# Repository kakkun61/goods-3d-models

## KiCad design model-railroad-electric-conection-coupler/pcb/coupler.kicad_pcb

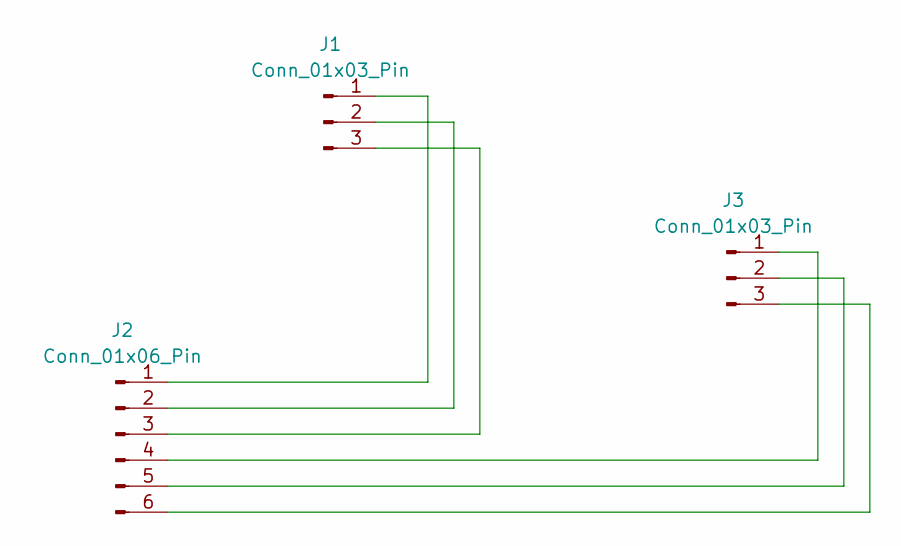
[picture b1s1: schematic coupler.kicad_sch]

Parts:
J1, J3: Conn_01x03_Pin; Pin_Side
J2: Conn_01x06_Pin; Molex_PicoBlade_53048-0610_1x06_P1.25mm_Horizontal

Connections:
unnamed: J1.1, J2.1
unnamed: J1.2, J2.2
unnamed: J1.3, J2.3
unnamed: J2.4, J3.1
unnamed: J2.5, J3.2
unnamed: J2.6, J3.3

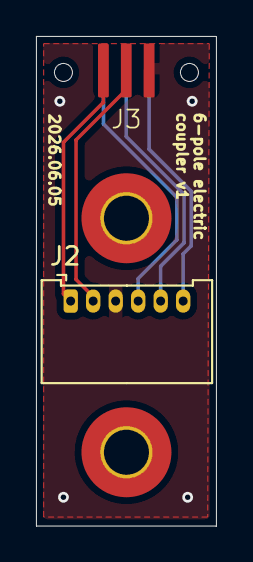
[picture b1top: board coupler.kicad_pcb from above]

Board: 2 copper layers, 10.0 x 27.2 mm, 3 parts (1 on the bottom side), 6 nets.

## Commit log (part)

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2025-02-07 水銀電池 PX27 互換アダプター
2025-02-07 ななめジョイナー
2025-04-19 Free CAD で AVR WRT 2 の外形をモデル化し始めた
2025-04-20 move
2025-04-21 Cover for AVR WRT 2 with Free CAD
2025-04-21 Restore すると Free CAD でエラーになってよめないのでやめる
2025-04-25 [pubot]大きさ試作
2025-04-25 AVR WRT 2 カバー ver.6
2025-04-27 [avrwrt2] 下駄
2025-05-01 update libs
2025-05-01 ignore Free CAD backup files
2025-05-01 ごみ箱 分割型の蓋 あまりうまいこといってない
2025-05-01 [trash-bin-separator] 接着する部分とかぶせる部分とに分離
    すぐ外れなくなるといいな
2025-05-02 はめ合いが固かった
    slop を大きく
    カバーの角をフィレット
2025-05-21 クレオスラックの引き出しを Free CAD で設計しなおした
2025-05-21 鉄道模型レイアウトのアイテム
2025-07-01 橋の支承のアップデート
2025-07-01 パソコンと Switch 2 で両方の音を出したい
2025-07-01 WIP トラスココンテナーの中で使う箱
2025-07-03 干渉しないよう高さに余裕をもたせる
2025-08-25 電子工作用の電線を巻いておくボビン
2025-08-25 WIP 学研 大人の科学 凸版印刷
2025-09-04 [お部屋鉄道模型レイアウトのドア部分のモジュールのコネクター] 概形はこんなもんかな
2025-09-06 数値入れして試作
2025-09-06 出力ファイルを無視
2025-09-07 出力修正をくりかえしてこれでいく
2026-04-30 コットにかけるフック
2026-05-01 コットにかけるフック v2
2026-05-01 ニッパーとかが開かないようにするやつ
2026-05-01 なんか変更
2026-05-01 タミヤ 楽しい工作シリーズ モノレール の関連品
2026-05-24 鉄道模型用のカプラー WIP
2026-06-02 鉄道模型用の通電カプラー PCB 版 WIP
2026-06-05 鉄道模型用の通電カプラー PCB 版 v1
2026-06-05 コーナンのすのこに付ける脚（だいぶ前に作った）
2026-06-05 Kensington Slimblade の球の周りの部分（前に作った）
